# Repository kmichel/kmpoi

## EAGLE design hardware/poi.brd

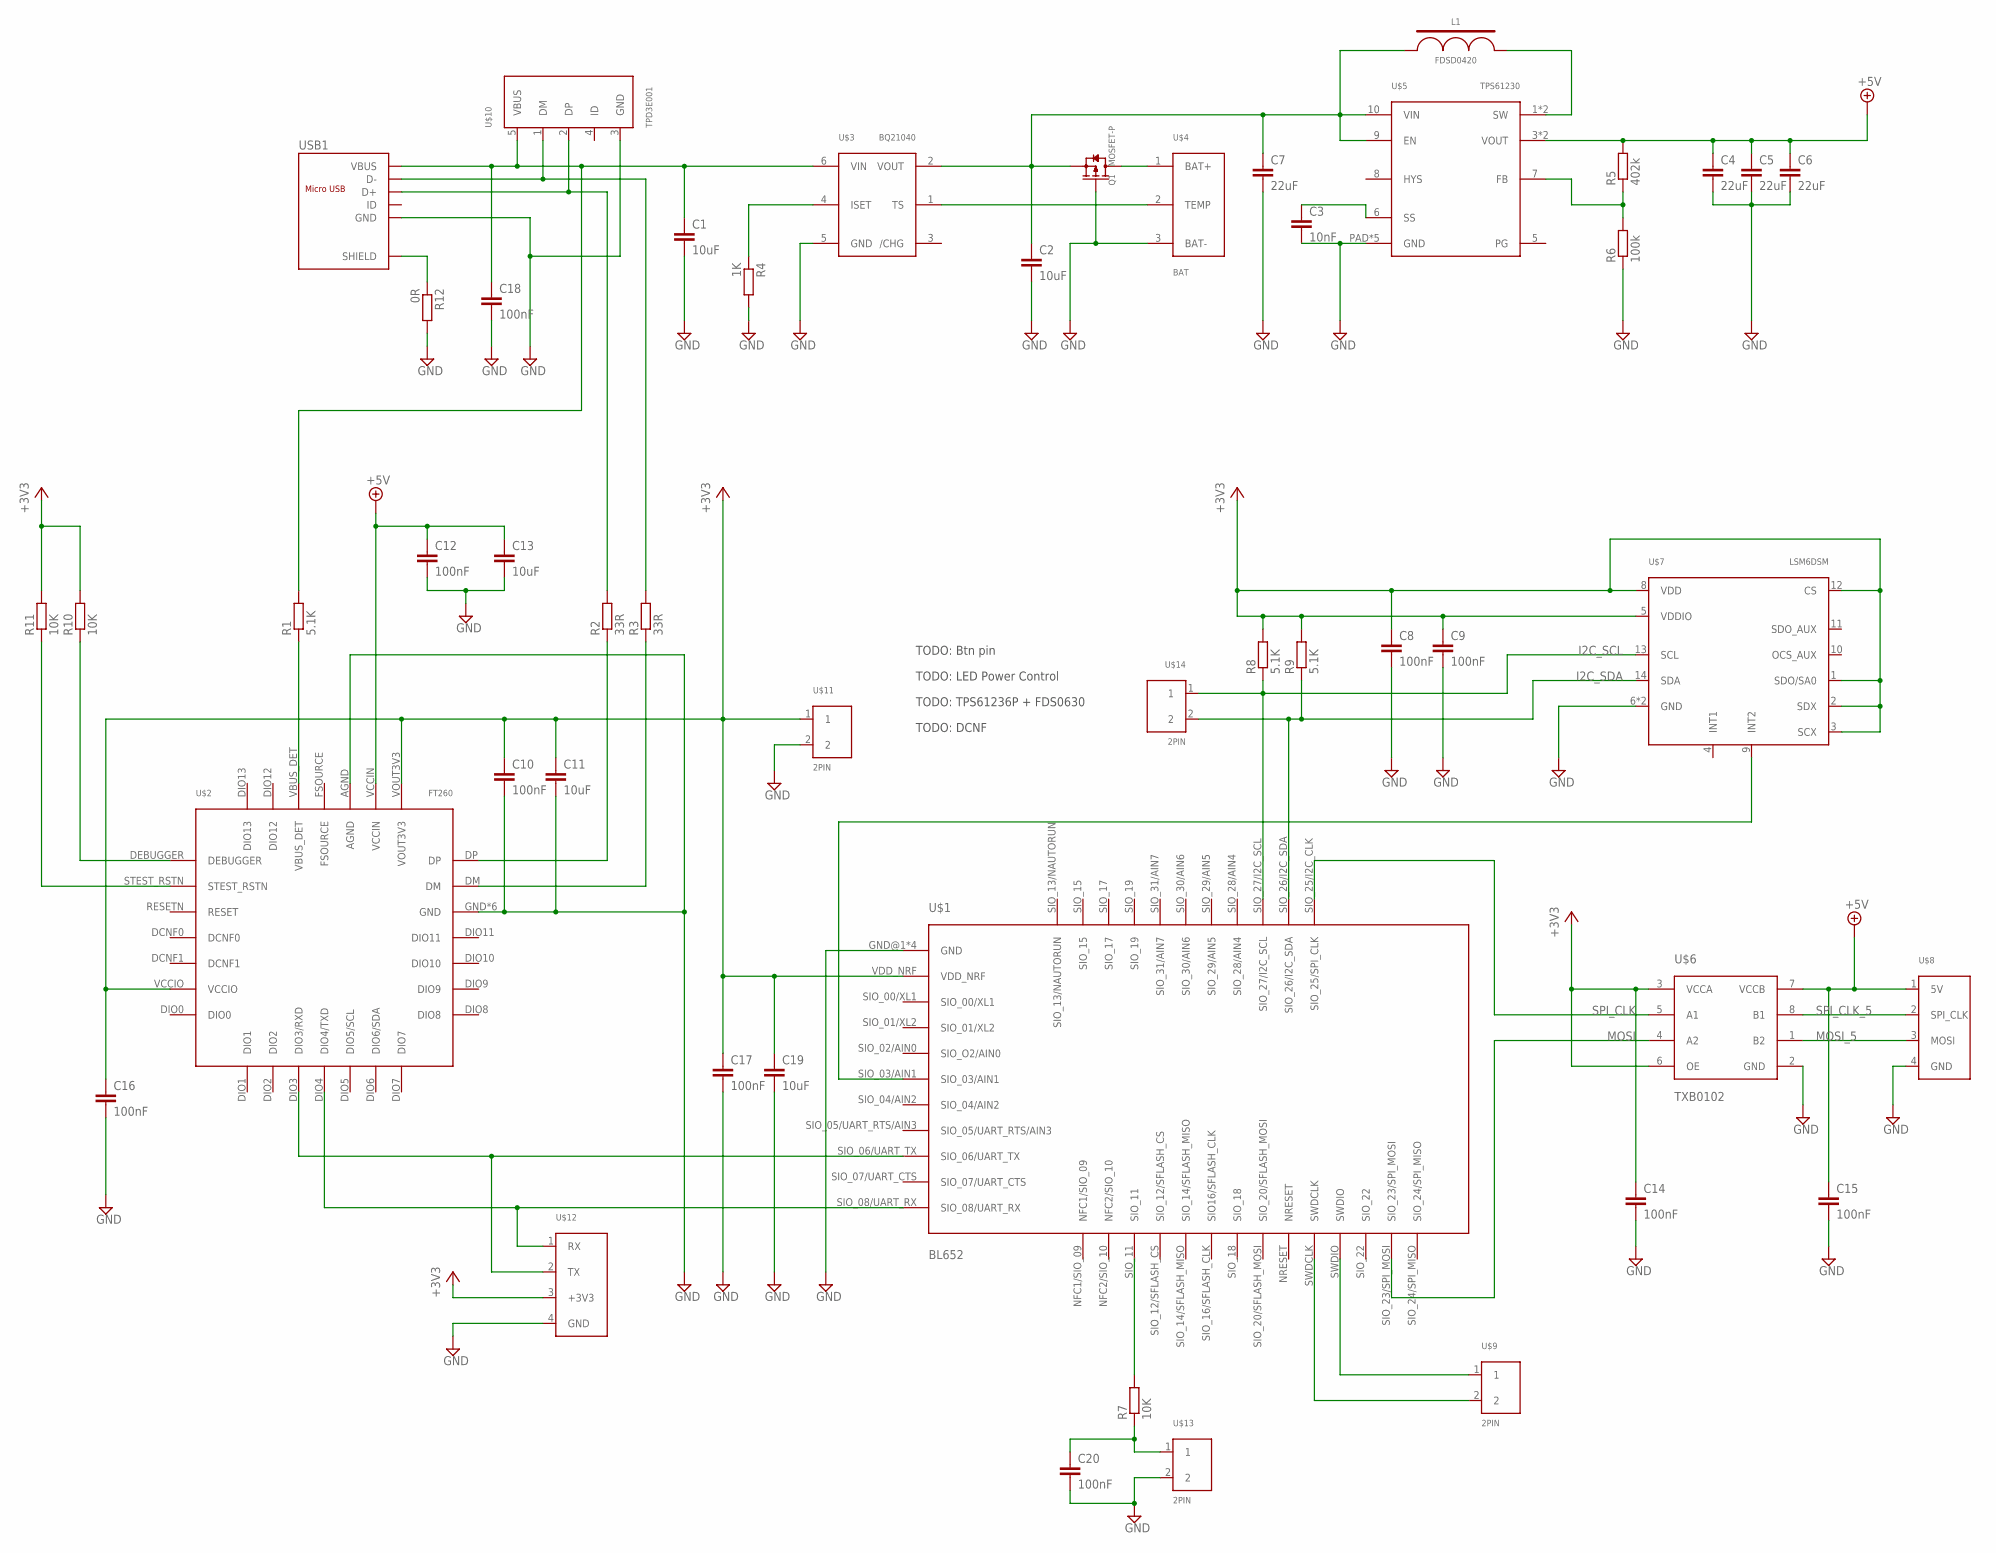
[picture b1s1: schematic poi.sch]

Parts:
C1, C2, C11, C13, C19: 10uF; C0603
C3: 10nF; C0603
C4, C5, C6, C7: 22uF; C0603
C8, C9, C10, C12, C14, C15, C16, C17, C18, C20: 100nF; C0603
L1: FDSD0420
Q1: MOSFET-P; SOT-23; MPN PMV65XPEA
R1, R8, R9: 5.1K; R0603
R2, R3: 33R; R0603
R4: 1K; R0603
R5: 402k; R0603
R6: 100k; R0603
R7, R10, R11: 10K; R0603
R12: 0R; R0603
U$1: BL652
U$2: FT260; WQFN-28
U$3: BQ21040; SOT23-6
U$4: BAT; 3PIN
U$5: TPS61230; VSON-10
U$6: TXB0102; VSSOP-8
U$7: LSM6DSM; LGA-14L
U$8: SPI-4PIN; 4PIN
U$9, U$11, U$13, U$14: 2PIN
U$10: TPD3E001; SOT-553
U$12: UART-4PIN; 4PIN
USB1: ZX62-B-5PA

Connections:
+3V3: C8.1, C9.1, C10.1, C11.1, C14.1, C16.1, C17.1, C19.1, R8.2, R9.2, R10.2, R11.2, U$1.VDD_NRF, U$2.VCCIO, U$2.VOUT3V3, U$6.3 (VCCA), U$6.6 (OE), U$7.1 (SDO/SA0), U$7.2 (SDX), U$7.3 (SCX), U$7.5 (VDDIO), U$7.8 (VDD), U$7.12 (CS), U$11.1, U$12.3 (+3V3)
+5V: C4.1, C5.1, C6.1, C12.1, C13.1, C15.1, R5.2, U$2.VCCIN, U$5.3 (VOUT), U$5.4 (VOUT), U$6.7 (VCCB), U$8.1 (5V)
BT_RX: U$1.SIO_08/UART_RX, U$2.DIO4 (DIO4/TXD), U$12.1 (RX)
BT_TX: U$1.SIO_06/UART_TX, U$2.DIO3 (DIO3/RXD), U$12.2 (TX)
DEBUGGER: R10.1, U$2.DEBUGGER
FB: R5.1, R6.2, U$5.7 (FB)
GND: C1.2, C2.2, C3.2, C4.2, C5.2, C6.2, C7.2, C8.2, C9.2, C10.2, C11.2, C12.2, C13.2, C14.2, C15.2, C16.2, C17.2, C18.2, C19.2, C20.2, Q1.1 (G), R4.2, R6.1, R12.2, U$1.GND@1 (GND), U$1.GND@2 (GND), U$1.GND@3 (GND), U$1.GND@4 (GND), U$2.AGND, U$2.GND, U$2.PAD (GND), U$2.V1 (GND), U$2.V2 (GND), U$2.V3 (GND), U$2.V4 (GND), U$3.5 (GND), U$4.3 (BAT-), U$5.PAD (GND), U$5.V1 (GND), U$5.V2 (GND), U$5.V3 (GND), U$5.V4 (GND), U$6.2 (GND), U$7.6 (GND), U$7.7 (GND), U$8.4 (GND), U$10.3 (GND), U$11.2, U$12.4 (GND), U$13.2, USB1.5 (GND)
I2C_SCL: R8.1, U$1.SIO_27/I2C_SCL, U$7.13 (SCL), U$14.1
I2C_SDA: R9.1, U$1.SIO_26/I2C_SDA, U$7.14 (SDA), U$14.2
INT2: U$1.SIO_03/AIN1, U$7.9 (INT2)
ISET: R4.1, U$3.4 (ISET)
MOSI: U$1.SIO_23/SPI_MOSI, U$6.4 (A2)
MOSI_5: U$6.1 (B2), U$8.3 (MOSI)
NTC: U$3.1 (TS), U$4.2 (TEMP)
PBIN: R7.2, U$1.SIO_11
PBOUT: C20.1, R7.1, U$13.1
SHIELD: R12.1, USB1.P1 (SHIELD), USB1.P2 (SHIELD), USB1.P3 (SHIELD), USB1.P4 (SHIELD), USB1.P5 (SHIELD), USB1.P6 (SHIELD)
SPI_CLK: U$1.SIO_25/I2C_CLK (SIO_25/SPI_CLK), U$6.5 (A1)
SPI_CLK_5: U$6.8 (B1), U$8.2 (SPI_CLK)
SS: C3.1, U$5.6 (SS)
STEST_RSTN: R11.1, U$2.STEST_RSTN
SW: L1.2, U$5.1 (SW), U$5.2 (SW)
SWDCLK: U$1.SWDCLK, U$9.2
SWDIO: U$1.SWDIO, U$9.1
USB_DM: R3.1, U$2.DM
USB_DM_OUT: R3.2, U$10.1 (DM), USB1.2 (D-)
USB_DP: R2.1, U$2.DP
USB_DP_OUT: R2.2, U$10.2 (DP), USB1.3 (D+)
VBAT: C2.1, C7.1, L1.1, Q1.2 (S), U$3.2 (VOUT), U$5.9 (EN), U$5.10 (VIN)
VBAT_RAW: Q1.3 (D), U$4.1 (BAT+)
VBUS: C1.1, C18.1, R1.2, U$3.6 (VIN), U$10.5 (VBUS), USB1.1 (VBUS)
VBUS_DET: R1.1, U$2.VBUS_DET

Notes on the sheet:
TODO: DCNF
TODO: TPS61236P + FDS0630
TODO: LED Power Control
TODO: Btn pin

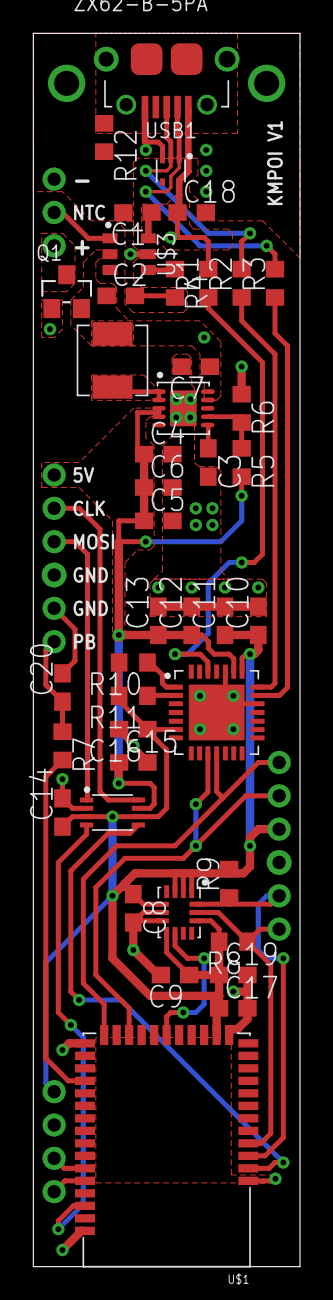
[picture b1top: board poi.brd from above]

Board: 2 copper layers, 16.0 x 74.0 mm, 49 parts (1 on the bottom side), 32 nets.

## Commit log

2017-05-11 Add eagle files
